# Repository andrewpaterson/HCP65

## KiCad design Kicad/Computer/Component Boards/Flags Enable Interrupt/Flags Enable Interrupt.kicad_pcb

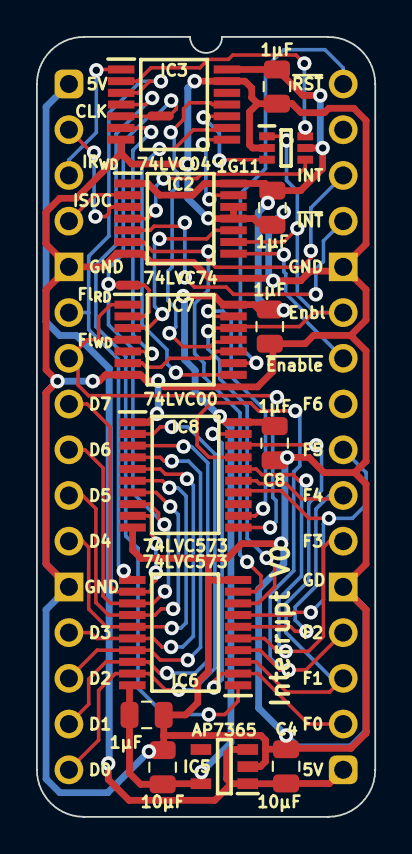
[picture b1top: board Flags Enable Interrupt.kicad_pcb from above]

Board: 2 copper layers, 18.8 x 43.3 mm, 17 parts (0 on the bottom side), 40 nets.

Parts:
C1, C2, C7, C8, C9: 1μF; C_0805
C4, C5: 10µF; C_0805
IC1: 74LVC1G11GW-Q100H; SOP65P210X110-6N
IC2: 74LVC74APW,118; SOP65P640X110-14N
IC3: 74LVC04APW,118; SOP65P640X110-14N
IC5: AP7365-33WG-7; SOT95P285X130-5N
IC6, IC8: 74LVC573APW,118; SOP65P640X110-20N
IC7: 74LVC00APW,112; SOP65P640X110-14N
J1: Board 2x16 W15.24mm; DIP-32_Board_W15.24mm
NT1, NT2: NetTie_2; NetTie-2_SMD_Pad0.5mm

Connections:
5V: C4.1, IC5.1 (6VIn), IC5.3 (EN), J1.1, J1.17
/3.3V: C1.1, C2.1, C5.1, C7.1, C8.1, C9.1, IC1.5 (3V), IC2.1 (~1RD), IC2.14 (3V), IC3.14 (3V), IC5.5 (3.3VOut), IC6.20 (3V), IC7.14 (3V), IC8.20 (3V)
/Enable Bit High: IC7.2 (1B), NT1.2
/Enable Bit_Low: IC3.5 (3A), NT2.2
/F_{Interrupt Enable}: IC7.13 (4B), IC8.12 (Q7)
/Interrupt Enable: IC1.3 (B), IC3.10 (5Y)
/Set Disable: IC3.9 (4A), IC7.8 (3Y)
/~Clear Interrupt: IC1.4 (Y), IC2.4 (~1SD)
/~Enable Bit: IC3.6 (3Y), IC7.5 (2B)
/~Interrupt Enable: IC3.11 (5A), IC7.11 (4Y)
/~Read Flags: IC3.4 (2Y), IC6.1 (~OE)
/~Set Disable: IC2.13 (~2RD), IC3.8 (4Y)
/~Set Enable: IC2.10 (~2SD), IC7.3 (1Y)
/~Write Clear Interrupt: IC1.6 (C), IC3.2 (1Y)
CLK: IC2.3 (1CP), J1.2
D0: IC6.19 (Q0), IC8.2 (D0), J1.16
D1: IC6.18 (Q1), IC8.3 (D1), J1.15
D2: IC6.17 (Q2), IC8.4 (D2), J1.14
D3: IC6.16 (Q3), IC8.5 (D3), J1.13
D4: IC6.15 (Q4), IC8.6 (D4), J1.11
D5: IC6.14 (Q5), IC8.7 (D5), J1.10
D6: IC6.13 (Q6), IC8.8 (D6), J1.9, NT1.1, NT2.1
D7: IC6.12 (Q7), IC8.9 (D7), J1.8
Enable: IC1.1 (A), IC2.9 (2Q), IC6.8 (D6), IC7.12 (4A), J1.27
F0: IC6.2 (D0), IC8.19 (Q0), J1.18
F1: IC6.3 (D1), IC8.18 (Q1), J1.19
F2: IC6.4 (D2), IC8.17 (Q2), J1.20
F3: IC6.5 (D3), IC8.16 (Q3), J1.22
F4: IC6.6 (D4), IC8.15 (Q4), J1.23
F5: IC6.7 (D5), IC8.14 (Q5), J1.24
GND: C1.2, C2.2, C4.2, C5.2, C7.2, C8.2, C9.2, IC1.2 (GND), IC2.7 (GND), IC2.11 (2CP), IC2.12 (2D), IC3.7 (GND), IC3.13 (6A), IC5.2 (GND), IC6.10 (GND), IC7.7 (GND), IC8.1 (~OE), IC8.10 (GND), J1.5, J1.12, J1.21, J1.28
Interrupt: IC2.6 (~1Q), IC6.9 (D7), J1.30
unnamed: IC7.6 (2Y), IC7.10 (3B)
Read Flags: IC3.3 (2A), IC6.11 (LE), J1.6
Write Clear Interrupt: IC3.1 (1A), J1.3
Write Flags: IC7.1 (1A), IC7.4 (2A), IC8.11 (LE), J1.7
~Enable: IC2.8 (~2Q), J1.26
~Interrupt: IC2.5 (1Q), J1.29
~Reset: IC7.9 (3A), J1.32
~Set Interrupt on CLK: IC2.2 (1D), J1.4

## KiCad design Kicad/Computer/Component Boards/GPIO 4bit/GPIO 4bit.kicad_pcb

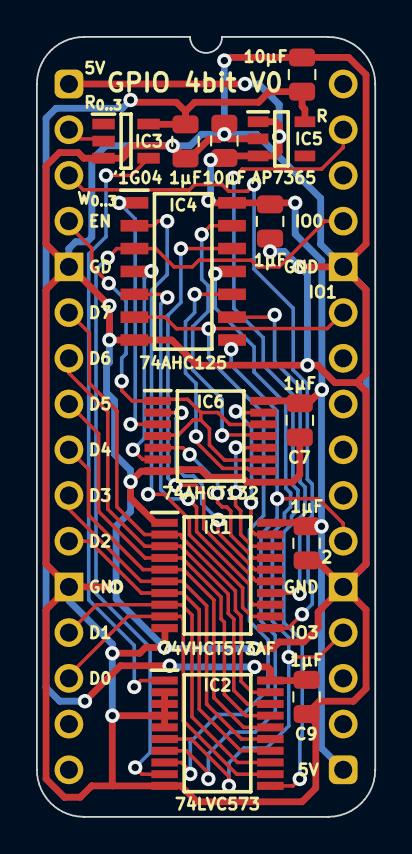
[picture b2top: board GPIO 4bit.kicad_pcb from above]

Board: 2 copper layers, 18.8 x 43.3 mm, 14 parts (0 on the bottom side), 32 nets.

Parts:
C1, C2, C6, C7, C9: 1μF; C_0805
C3, C4: 10µF; C_0805
IC1: 74VHCT573AFT; SOP65P640X120-20N
IC2: 74LVC573APW,118; SOP65P640X110-20N
IC3: 74LVC1G04GV,125; SOT95P275X110-5N
IC4: 74AHC125S14; SOIC127P600X173-14N
IC5: AP7365-33WG-7; SOT95P285X130-5N
IC6: SN74AHCT132PWR; SOP65P640X120-14N
J1: Board 2x16 W15.24mm; DIP-32_Board_W15.24mm

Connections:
5V: C1.1, C3.1, C6.1, C7.1, IC1.20 (5V), IC4.14 (VCC), IC5.1 (6VIn), IC5.3 (EN), IC6.14 (5V), J1.1, J1.17
/3.3V: C2.1, C4.1, C9.1, IC2.20 (3V), IC3.5 (3V), IC5.5 (3.3VOut)
/GD0: IC1.12 (Q7), IC4.2 (1A)
/GD1: IC1.13 (Q6), IC4.5 (2A)
/GD2: IC1.14 (Q5), IC4.9 (3A)
/GD3: IC1.15 (Q4), IC4.12 (4A)
/OE0: IC1.16 (Q3), IC6.2 (1B)
/OE1: IC1.17 (Q2), IC6.5 (2B)
/OE2: IC1.18 (Q1), IC6.10 (3B)
/OE3: IC1.19 (Q0), IC6.13 (4B)
D0: IC1.9 (D7), IC2.12 (Q7), J1.14
D1: IC1.8 (D6), IC2.13 (Q6), J1.13
D2: IC1.7 (D5), IC2.14 (Q5), J1.11
D3: IC1.6 (D4), IC2.15 (Q4), J1.10
D4: IC1.5 (D3), IC2.16 (Q3), J1.9
D5: IC1.4 (D2), IC2.17 (Q2), J1.8
D6: IC1.3 (D1), IC2.18 (Q1), J1.7
D7: IC1.2 (D0), IC2.19 (Q0), J1.6
Enable: IC6.1 (1A), IC6.4 (2A), IC6.9 (3A), IC6.12 (4A), J1.4
GND: C1.2, C2.2, C3.2, C4.2, C6.2, C7.2, C9.2, IC1.1 (~OE), IC1.10 (GND), IC2.2 (D0), IC2.3 (D1), IC2.4 (D2), IC2.5 (D3), IC2.10 (GND), IC3.3 (GND), IC4.7 (GND), IC5.2 (GND), IC6.7 (GND), J1.5, J1.12, J1.21, J1.28
GPIO0: IC2.9 (D7), IC4.3 (1Y), J1.29
GPIO1: IC2.8 (D6), IC4.6 (2Y), J1.27
GPIO2: IC2.7 (D5), IC4.8 (3Y), J1.22
GPIO3: IC2.6 (D4), IC4.11 (4Y), J1.20
unnamed: IC2.1 (~OE), IC3.4 (Y)
unnamed: IC4.1 (1~OE), IC6.3 (1Y)
unnamed: IC4.4 (2~OE), IC6.6 (2Y)
unnamed: IC4.10 (3~OE), IC6.8 (3Y)
unnamed: IC4.13 (4~OE), IC6.11 (4Y)
Read: IC2.11 (LE), J1.31
Read GD _{0..3}: IC3.2 (A), J1.2
Write GD _{0..3}: IC1.11 (LE), J1.3

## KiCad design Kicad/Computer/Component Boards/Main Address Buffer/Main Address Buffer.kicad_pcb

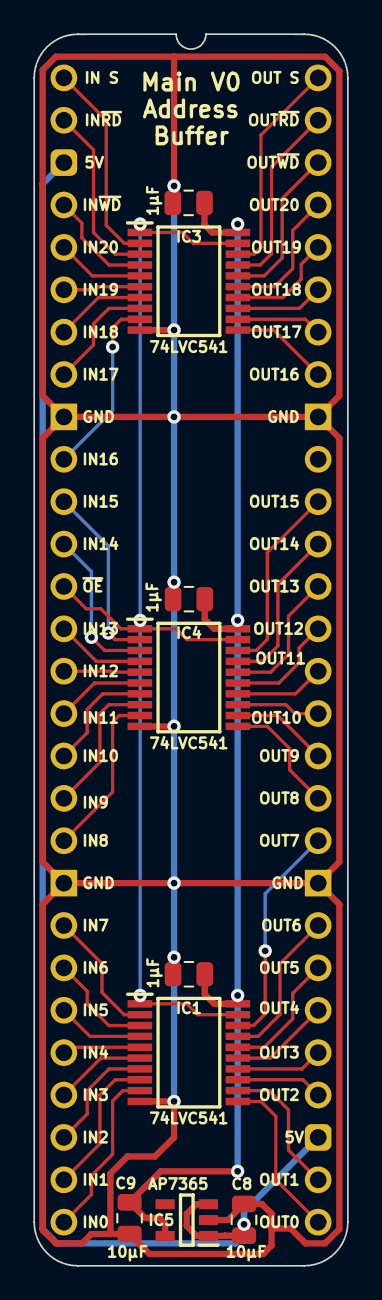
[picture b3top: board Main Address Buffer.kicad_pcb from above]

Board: 2 copper layers, 18.8 x 73.8 mm, 10 parts (0 on the bottom side), 52 nets.

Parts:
C1, C2, C3: 1μF; C_0805
C8, C9: 10µF; C_0805
IC1, IC3, IC4: 74LVC541APW,118; SOP65P640X110-20N
IC5: AP7365-33WG-7; SOT95P285X130-5N
J2: Board 2x28 W15.24mm; DIP-56_Board_W15.24mm

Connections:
5V: C8.1, IC5.1 (6VIn), IC5.3 (EN), J2.3, J2.31
/3.3V: C1.1, C2.1, C3.1, C9.1, IC1.20 (3V), IC3.20 (3V), IC4.20 (3V), IC5.5 (3.3VOut)
AM0: IC1.9 (A7), J2.28
AM1: IC1.8 (A6), J2.27
AM2: IC1.7 (A5), J2.26
AM3: IC1.6 (A4), J2.25
AM4: IC1.5 (A3), J2.24
AM5: IC1.4 (A2), J2.23
AM6: IC1.3 (A1), J2.22
AM7: IC1.2 (A0), J2.21
AM8: IC4.9 (A7), J2.19
AM9: IC4.8 (A6), J2.18
AM10: IC4.7 (A5), J2.17
AM11: IC4.6 (A4), J2.16
AM12: IC4.5 (A3), J2.15
AM13: IC4.4 (A2), J2.14
AM14: IC4.3 (A1), J2.12
AM15: IC4.2 (A0), J2.11
AM16: IC3.9 (A7), J2.10
AM17: IC3.8 (A6), J2.8
AM18: IC3.7 (A5), J2.7
AM19: IC3.6 (A4), J2.6
AM20: IC3.5 (A3), J2.5
AS0: IC1.11 (Y7), J2.29
AS1: IC1.12 (Y6), J2.30
AS2: IC1.13 (Y5), J2.32
AS3: IC1.14 (Y4), J2.33
AS4: IC1.15 (Y3), J2.34
AS5: IC1.16 (Y2), J2.35
AS6: IC1.17 (Y1), J2.36
AS7: IC1.18 (Y0), J2.38
AS8: IC4.11 (Y7), J2.39
AS9: IC4.12 (Y6), J2.40
AS10: IC4.13 (Y5), J2.41
AS11: IC4.14 (Y4), J2.42
AS12: IC4.15 (Y3), J2.43
AS13: IC4.16 (Y2), J2.44
AS14: IC4.17 (Y1), J2.45
AS15: IC4.18 (Y0), J2.46
AS16: IC3.11 (Y7), J2.49
AS17: IC3.12 (Y6), J2.50
AS18: IC3.13 (Y5), J2.51
AS19: IC3.14 (Y4), J2.52
AS20: IC3.15 (Y3), J2.53
GND: C1.2, C2.2, C3.2, C8.2, C9.2, IC1.10 (GND), IC3.10 (GND), IC4.10 (GND), IC5.2 (GND), J2.9, J2.20, J2.37, J2.48
MT: IC3.2 (A0), J2.1
M~RD: IC3.3 (A1), J2.2
M~WD: IC3.4 (A2), J2.4
ST: IC3.18 (Y0), J2.56
S~RD: IC3.17 (Y1), J2.55
S~WD: IC3.16 (Y2), J2.54
~OE: IC1.1 (~OE1), IC1.19 (~OE2), IC3.1 (~OE1), IC3.19 (~OE2), IC4.1 (~OE1), IC4.19 (~OE2), J2.13

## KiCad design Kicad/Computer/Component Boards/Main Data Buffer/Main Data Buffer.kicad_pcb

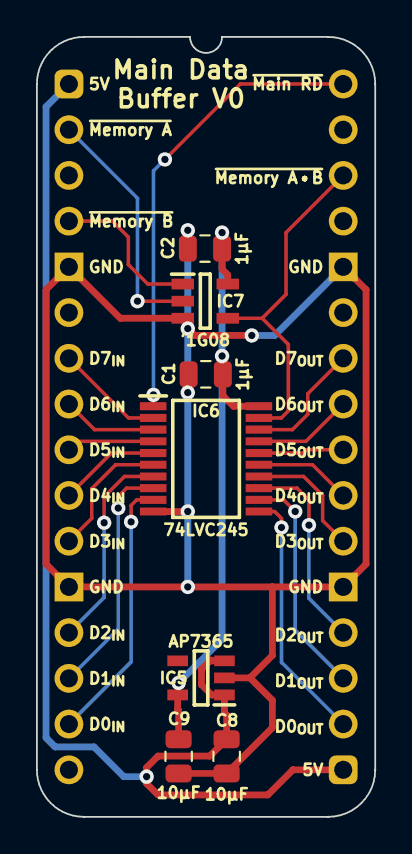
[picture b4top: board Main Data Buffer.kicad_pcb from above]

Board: 2 copper layers, 18.8 x 43.3 mm, 8 parts (0 on the bottom side), 23 nets.

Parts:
C1, C2: 1μF; C_0805
C8, C9: 10µF; C_0805
IC5: AP7365-33WG-7; SOT95P285X130-5N
IC6: 74LVC245AT20; SOP65P640X120-20N
IC7: 74LVC1G08GV,125; SOT95P275X110-5N
J5: Board 2x16 W15.24mm; DIP-32_Board_W15.24mm

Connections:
5V: C8.1, IC5.1 (6VIn), IC5.3 (EN), J5.1, J5.17
/3.3V: C1.1, C2.1, C9.1, IC5.5 (3.3VOut), IC6.20 (3V), IC7.5 (3V)
DM0: IC6.9 (A7), J5.15
DM1: IC6.8 (A6), J5.14
DM2: IC6.7 (A5), J5.13
DM3: IC6.6 (A4), J5.11
DM4: IC6.5 (A3), J5.10
DM5: IC6.4 (A2), J5.9
DM6: IC6.3 (A1), J5.8
DM7: IC6.2 (A0), J5.7
DS0: IC6.11 (B7), J5.18
DS1: IC6.12 (B6), J5.19
DS2: IC6.13 (B5), J5.20
DS3: IC6.14 (B4), J5.22
DS4: IC6.15 (B3), J5.23
DS5: IC6.16 (B2), J5.24
DS6: IC6.17 (B1), J5.25
DS7: IC6.18 (B0), J5.26
GND: C1.2, C2.2, C8.2, C9.2, IC5.2 (GND), IC6.10 (GND), IC7.3 (GND), J5.5, J5.12, J5.21, J5.28
~Main RD: IC6.1 (DIR), J5.32
~Memory A: IC7.2 (A), J5.2
~Memory A•B: IC6.19 (~OE), IC7.4 (Y), J5.30
~Memory B: IC7.1 (B), J5.4

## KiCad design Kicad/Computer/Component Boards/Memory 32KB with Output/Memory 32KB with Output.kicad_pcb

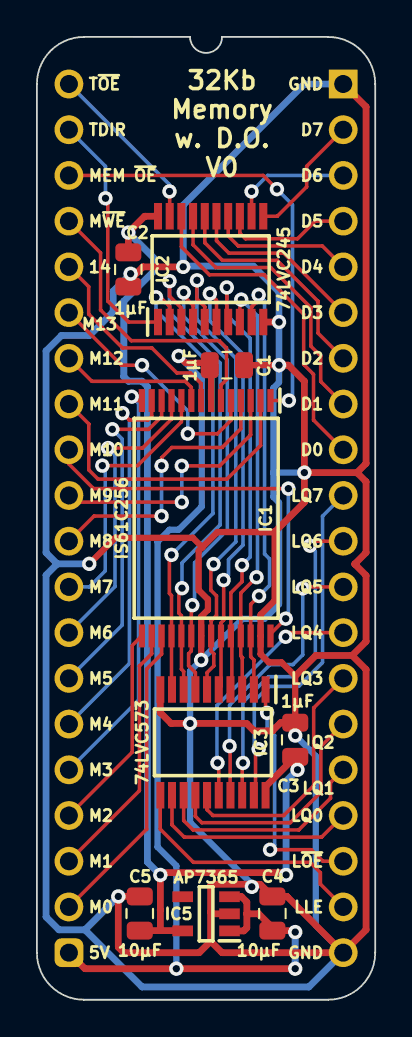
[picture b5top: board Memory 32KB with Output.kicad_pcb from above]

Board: 2 copper layers, 18.8 x 53.5 mm, 10 parts (0 on the bottom side), 48 nets.

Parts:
C1, C2, C3: 1μF; C_0805
C4, C5: 10µF; C_0805
IC1: IS61C256AL-12TLI; SOP55P1340X120-28N
IC2: 74LVC245AT20; SOP65P640X120-20N
IC3: 74LVC573APW,118; SOP65P640X110-20N
IC5: AP7365-33WG-7; SOT95P285X130-5N
J1: Board 2x20 W22.86mm; DIP-40_Board_W15.24mm_Alt

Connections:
5V: C1.1, C4.1, IC1.7 (5V), IC5.1 (6VIn), IC5.3 (EN), J1.20
/3.3V: C2.1, C3.1, C5.1, IC2.20 (3V), IC3.20 (3V), IC5.5 (3.3VOut)
/DM0: IC1.18 (D0), IC2.2 (A0), IC3.9 (D7)
/DM1: IC1.19 (D1), IC2.3 (A1), IC3.8 (D6)
/DM2: IC1.20 (D2), IC2.4 (A2), IC3.7 (D5)
/DM3: IC1.22 (D3), IC2.5 (A3), IC3.6 (D4)
/DM4: IC1.23 (D4), IC2.6 (A4), IC3.5 (D3)
/DM5: IC1.24 (D5), IC2.7 (A5), IC3.4 (D2)
/DM6: IC1.25 (D6), IC2.8 (A6), IC3.3 (D1)
/DM7: IC1.26 (D7), IC2.9 (A7), IC3.2 (D0)
D0: IC2.18 (B0), J1.32
D1: IC2.17 (B1), J1.33
D2: IC2.16 (B2), J1.34
D3: IC2.15 (B3), J1.35
D4: IC2.14 (B4), J1.36
D5: IC2.13 (B5), J1.37
D6: IC2.12 (B6), J1.38
D7: IC2.11 (B7), J1.39
GND: C1.2, C2.2, C3.2, C4.2, C5.2, IC1.21 (GND), IC1.27 (~CE), IC2.10 (GND), IC3.10 (GND), IC5.2 (GND), J1.21, J1.40
LLE: IC3.11 (LE), J1.22
LQ0: IC3.12 (Q7), J1.24
LQ1: IC3.13 (Q6), J1.25
LQ2: IC3.14 (Q5), J1.26
LQ3: IC3.15 (Q4), J1.27
LQ4: IC3.16 (Q3), J1.28
LQ5: IC3.17 (Q2), J1.29
LQ6: IC3.18 (Q1), J1.30
LQ7: IC3.19 (Q0), J1.31
L~OE: IC3.1 (~OE), J1.23
M0: IC1.17 (A0), J1.19
M1: IC1.16 (A1), J1.18
M2: IC1.15 (A2), J1.17
M3: IC1.14 (A3), J1.16
M4: IC1.13 (A4), J1.15
M5: IC1.12 (A5), J1.14
M6: IC1.11 (A6), J1.13
M7: IC1.10 (A7), J1.12
M8: IC1.4 (A8), J1.11
M9: IC1.3 (A9), J1.10
M10: IC1.28 (A10), J1.9
M11: IC1.2 (A11), J1.8
M12: IC1.9 (A12), J1.7
M13: IC1.5 (A13), J1.6
M14: IC1.8 (A14), J1.5
M~OE: IC1.1 (~OE), J1.3
M~WE: IC1.6 (~WE), J1.4
TDIR: IC2.1 (DIR), J1.2
T~OE: IC2.19 (~OE), J1.1

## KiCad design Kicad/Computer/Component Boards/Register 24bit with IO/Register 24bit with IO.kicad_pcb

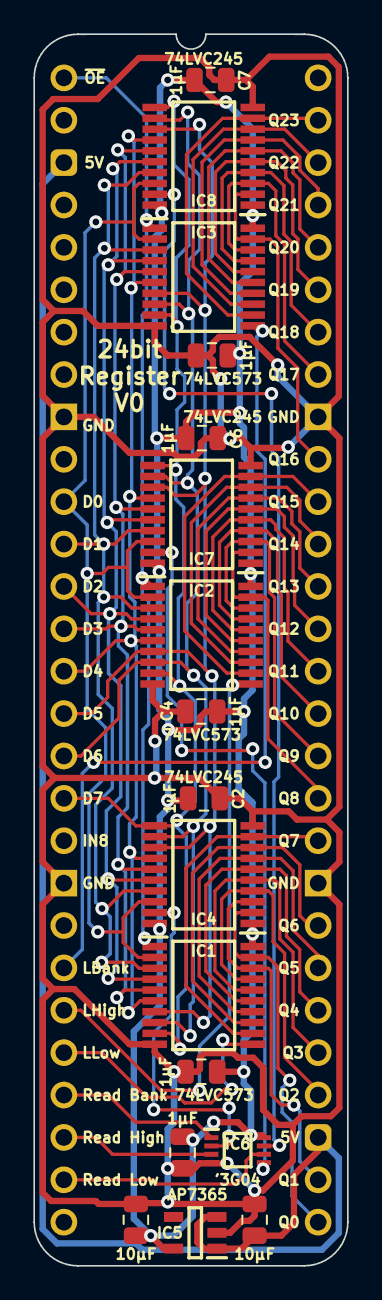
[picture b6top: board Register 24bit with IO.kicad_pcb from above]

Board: 2 copper layers, 18.8 x 73.8 mm, 18 parts (0 on the bottom side), 45 nets.

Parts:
C1, C2, C3, C4, C5, C6, C7: 1μF; C_0805
C8, C9: 10µF; C_0805
IC1, IC2, IC3: 74LVC573APW,118; SOP65P640X110-20N
IC4, IC7, IC8: 74LVC245AT20; SOP65P640X120-20N
IC5: AP7365-33WG-7; SOT95P285X130-5N
IC6: SN74LVC3G04DCUR; SOP50P310X90-8N
J2: Board 2x28 W15.24mm; DIP-56_Board_W15.24mm

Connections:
5V: C8.1, IC5.1 (6VIn), IC5.3 (EN), J2.3, J2.31
/3.3V: C1.1, C2.1, C3.1, C4.1, C5.1, C6.1, C7.1, C9.1, IC1.20 (3V), IC2.20 (3V), IC3.20 (3V), IC4.1 (DIR), IC4.20 (3V), IC5.5 (3.3VOut), IC6.8 (3V), IC7.1 (DIR), IC7.20 (3V), IC8.1 (DIR), IC8.20 (3V)
/~Read Bank: IC6.7 (1Y), IC8.19 (~OE)
/~Read High: IC6.5 (2Y), IC7.19 (~OE)
/~Read Low: IC4.19 (~OE), IC6.2 (3Y)
D0: IC1.2 (D0), IC2.2 (D0), IC3.2 (D0), IC4.18 (B0), IC7.18 (B0), IC8.18 (B0), J2.11
D1: IC1.3 (D1), IC2.3 (D1), IC3.3 (D1), IC4.17 (B1), IC7.17 (B1), IC8.17 (B1), J2.12
D2: IC1.4 (D2), IC2.4 (D2), IC3.4 (D2), IC4.16 (B2), IC7.16 (B2), IC8.16 (B2), J2.13
D3: IC1.5 (D3), IC2.5 (D3), IC3.5 (D3), IC4.15 (B3), IC7.15 (B3), IC8.15 (B3), J2.14
D4: IC1.6 (D4), IC2.6 (D4), IC3.6 (D4), IC4.14 (B4), IC7.14 (B4), IC8.14 (B4), J2.15
D5: IC1.7 (D5), IC2.7 (D5), IC3.7 (D5), IC4.13 (B5), IC7.13 (B5), IC8.13 (B5), J2.16
D6: IC1.8 (D6), IC2.8 (D6), IC3.8 (D6), IC4.12 (B6), IC7.12 (B6), IC8.12 (B6), J2.17
D7: IC1.9 (D7), IC2.9 (D7), IC3.9 (D7), IC4.11 (B7), IC7.11 (B7), IC8.11 (B7), J2.18
GND: C1.2, C2.2, C3.2, C4.2, C5.2, C6.2, C7.2, C8.2, C9.2, IC1.10 (GND), IC2.10 (GND), IC3.10 (GND), IC4.10 (GND), IC5.2 (GND), IC6.4 (GND), IC7.10 (GND), IC8.10 (GND), J2.9, J2.20, J2.37, J2.48
Latch Bank: IC3.11 (LE), J2.22
Latch High: IC2.11 (LE), J2.23
Latch Low: IC1.11 (LE), J2.24
Q0: IC1.19 (Q0), IC4.2 (A0), J2.29
Q1: IC1.18 (Q1), IC4.3 (A1), J2.30
Q2: IC1.17 (Q2), IC4.4 (A2), J2.32
Q3: IC1.16 (Q3), IC4.5 (A3), J2.33
Q4: IC1.15 (Q4), IC4.6 (A4), J2.34
Q5: IC1.14 (Q5), IC4.7 (A5), J2.35
Q6: IC1.13 (Q6), IC4.8 (A6), J2.36
Q7: IC1.12 (Q7), IC4.9 (A7), J2.38
Q8: IC2.19 (Q0), IC7.2 (A0), J2.39
Q9: IC2.18 (Q1), IC7.3 (A1), J2.40
Q10: IC2.17 (Q2), IC7.4 (A2), J2.41
Q11: IC2.16 (Q3), IC7.5 (A3), J2.42
Q12: IC2.15 (Q4), IC7.6 (A4), J2.43
Q13: IC2.14 (Q5), IC7.7 (A5), J2.44
Q14: IC2.13 (Q6), IC7.8 (A6), J2.45
Q15: IC2.12 (Q7), IC7.9 (A7), J2.46
Q16: IC3.19 (Q0), IC8.2 (A0), J2.47
Q17: IC3.18 (Q1), IC8.3 (A1), J2.49
Q18: IC3.17 (Q2), IC8.4 (A2), J2.50
Q19: IC3.16 (Q3), IC8.5 (A3), J2.51
Q20: IC3.15 (Q4), IC8.6 (A4), J2.52
Q21: IC3.14 (Q5), IC8.7 (A5), J2.53
Q22: IC3.13 (Q6), IC8.8 (A6), J2.54
Q23: IC3.12 (Q7), IC8.9 (A7), J2.55
Read Bank: IC6.1 (1A), J2.25
Read High: IC6.3 (2A), J2.26
Read Low: IC6.6 (3A), J2.27
~OE: IC1.1 (~OE), IC2.1 (~OE), IC3.1 (~OE), J2.1

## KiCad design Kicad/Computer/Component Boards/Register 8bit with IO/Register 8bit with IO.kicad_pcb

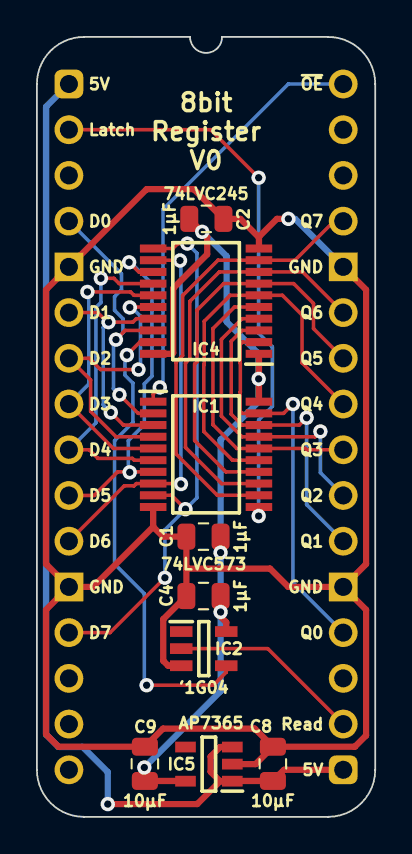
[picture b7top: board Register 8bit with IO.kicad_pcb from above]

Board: 2 copper layers, 18.8 x 43.3 mm, 10 parts (0 on the bottom side), 23 nets.

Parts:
C1, C2, C4: 1μF; C_0805
C8, C9: 10µF; C_0805
IC1: 74LVC573APW,118; SOP65P640X110-20N
IC2: 74LVC1G04GV,125; SOT95P275X110-5N
IC4: 74LVC245AT20; SOP65P640X120-20N
IC5: AP7365-33WG-7; SOT95P285X130-5N
J2: Board 2x16 W15.24mm; DIP-32_Board_W15.24mm

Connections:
5V: C8.1, IC5.1 (6VIn), IC5.3 (EN), J2.1, J2.17
/3.3V: C1.1, C2.1, C4.1, C9.1, IC1.20 (3V), IC2.5 (3V), IC4.1 (DIR), IC4.20 (3V), IC5.5 (3.3VOut)
/~Read: IC2.4 (Y), IC4.19 (~OE)
D0: IC1.2 (D0), IC4.18 (B0), J2.4
D1: IC1.3 (D1), IC4.17 (B1), J2.6
D2: IC1.4 (D2), IC4.16 (B2), J2.7
D3: IC1.5 (D3), IC4.15 (B3), J2.8
D4: IC1.6 (D4), IC4.14 (B4), J2.9
D5: IC1.7 (D5), IC4.13 (B5), J2.10
D6: IC1.8 (D6), IC4.12 (B6), J2.11
D7: IC1.9 (D7), IC4.11 (B7), J2.13
GND: C1.2, C2.2, C4.2, C8.2, C9.2, IC1.10 (GND), IC2.3 (GND), IC4.10 (GND), IC5.2 (GND), J2.5, J2.12, J2.21, J2.28
Latch: IC1.11 (LE), J2.2
Q0: IC1.19 (Q0), IC4.2 (A0), J2.20
Q1: IC1.18 (Q1), IC4.3 (A1), J2.22
Q2: IC1.17 (Q2), IC4.4 (A2), J2.23
Q3: IC1.16 (Q3), IC4.5 (A3), J2.24
Q4: IC1.15 (Q4), IC4.6 (A4), J2.25
Q5: IC1.14 (Q5), IC4.7 (A5), J2.26
Q6: IC1.13 (Q6), IC4.8 (A6), J2.27
Q7: IC1.12 (Q7), IC4.9 (A7), J2.29
Read: IC2.2 (A), J2.18
~OE: IC1.1 (~OE), J2.32

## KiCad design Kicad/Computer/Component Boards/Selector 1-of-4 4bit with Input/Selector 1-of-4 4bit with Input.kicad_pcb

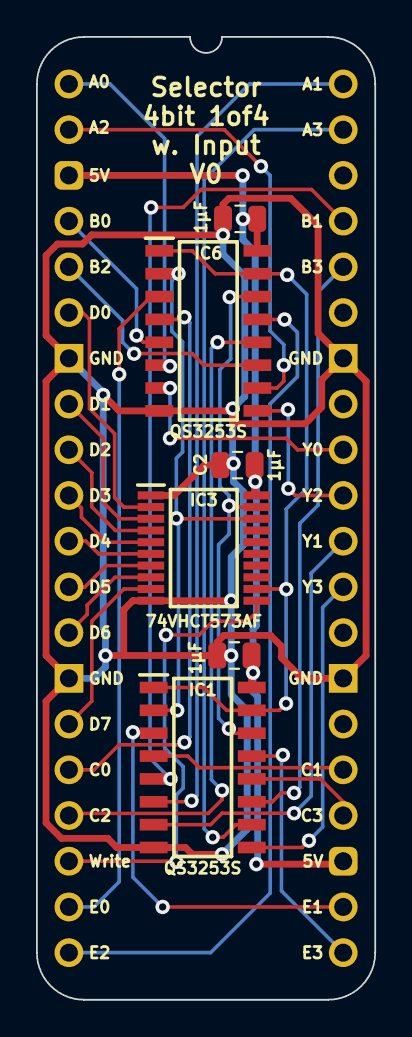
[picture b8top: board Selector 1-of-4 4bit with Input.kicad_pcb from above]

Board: 2 copper layers, 18.8 x 53.5 mm, 7 parts (0 on the bottom side), 34 nets.

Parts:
C1, C2, C3: 1μF; C_0805
IC1, IC6: QS3253S1G; SOIC127P602X173-16N
IC3: 74VHCT573AFT; SOP65P640X120-20N
J2: Board 2x20 W15.24mm; DIP-40_Board_W15.24mm

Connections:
5V: C1.1, C2.1, C3.1, IC1.16 (5V), IC3.20 (5V), IC6.16 (5V), J2.3, J2.23
/S0: IC1.14 (S0), IC3.19 (Q0), IC6.14 (S0)
/S1: IC1.2 (S1), IC3.18 (Q1), IC6.2 (S1)
/~E: IC1.1 (~EA), IC1.15 (~EB), IC3.12 (Q7), IC6.1 (~EA), IC6.15 (~EB)
A0: IC6.6 (I0A), J2.1
A1: IC1.6 (I0A), J2.40
A2: IC6.10 (I0B), J2.2
A3: IC1.10 (I0B), J2.39
B0: IC6.5 (I1A), J2.4
B1: IC1.5 (I1A), J2.37
B2: IC6.11 (I1B), J2.5
B3: IC1.11 (I1B), J2.36
C0: IC6.4 (I2A), J2.16
C1: IC1.4 (I2A), J2.25
C2: IC6.12 (I2B), J2.17
C3: IC1.12 (I2B), J2.24
D0: IC3.2 (D0), J2.6
D1: IC3.3 (D1), J2.8
D2: IC3.4 (D2), J2.9
D3: IC3.5 (D3), J2.10
D4: IC3.6 (D4), J2.11
D5: IC3.7 (D5), J2.12
D6: IC3.8 (D6), J2.13
D7: IC3.9 (D7), J2.15
E0: IC6.3 (I3A), J2.19
E1: IC1.3 (I3A), J2.22
E2: IC6.13 (I3B), J2.20
E3: IC1.13 (I3B), J2.21
GND: C1.2, C2.2, C3.2, IC1.8 (GND), IC3.1 (~OE), IC3.10 (GND), IC6.8 (GND), J2.7, J2.14, J2.27, J2.34
Write Select: IC3.11 (LE), J2.18
Y0: IC6.7 (YA), J2.32
Y1: IC1.7 (YA), J2.30
Y2: IC6.9 (YB), J2.31
Y3: IC1.9 (YB), J2.29
